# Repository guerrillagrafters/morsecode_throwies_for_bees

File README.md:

# morsecode_throwies_for_bees
This project builds off of the original throwie by Graffiti Research Labs (www.graffitiresearchlab.com), and the subsequent development of the morse code throwie using the ATTINY (http://www.instructables.com/id/Throwduino-Basic-Light-Sensing-Flashing-Throwie-/). Our morse code blinks out the names of fruits in Morse code. Use Ultraviolet LEDs to attract bees.

A lot more work could be done to make this code lighter. We welcome development!

What's needed:
 - Arduino or ATTiny programmer (Sparkfun sells one)
 - ATTiny85 (45 okay with some adjustments)
 - LEDs - we use Ultraviolet LEDs
 - Lithium coin cell battery
 - perf board for circuit, or custom designed circuit
 - electrical wire
 
 optional:
  - toggle switch
  - 270 or 330 resistor

To begin:
1) Make sure the Arduino programming environment is version 1.6.0 or above
2) In Arduino> Preferences, add the David Mellis attiny to boards manager URLs
     - Note: you might need to update boards.txt, manually writing in attiny45usbtinyisp.buildboard = COTE_ATTINY45USBTINYISP,        etc. 
3) Hook up your Arduino microcontroller, and run Arduino ISP from File> Examples
   - In the Tools menu, the board is set to "Arduino/ Genuino Uno", port is set to Arduino/ Uno, and the Programmer is AVR ISP
   - This is establishing the Arduino as a programmer for our ATTIny
4) Next, set up your ATTiny 85 on a breadboard. Schematic and image:
From High Low Tech's <a href="http://highlowtech.org/?p=1706">Arduino board as ATtiny programmer</a> article

From High Low Tech's <a href="http://highlowtech.org/?p=1695">Programming an ATtiny w/ Arduino 1.6 (or 1.0)</a> article

    - pins:
        - ATtiny Pin 2 to Arduino Pin 13 
        - ATtiny Pin 1 to Arduino Pin 12 
        - ATtiny Pin 0 to Arduino Pin 11
        - ATtiny Reset Pin to Arduino Pin 10 
   
5) Restart the Arduino code environment
6) In Tools> set the Board to ATTiny 25/45/85; Processor: ATTiny 85; Clock: Internal 1Mhz; Programmer: Arduino as ISP

6) Run "Blink" from File>Examples>Basics -- Change pin 13 to pin 0.
7) If blink is working, then we can now upload our morse code arduino code (above)
8) The basic schematic for the morse code throwie is here. I've also shared the eagle schematic and pcb design as a demonstration of how a creative design could be implemented using othermill. 

testing....

testing....

(Othermill can't handle these sharp lines, but hopefully will someday... this could be painted using conductive paint, or...)

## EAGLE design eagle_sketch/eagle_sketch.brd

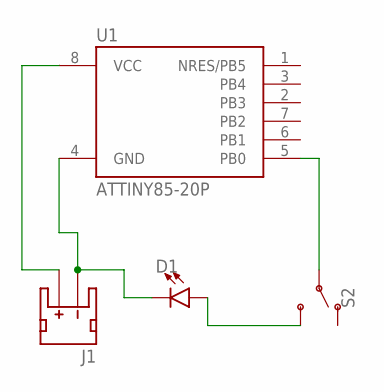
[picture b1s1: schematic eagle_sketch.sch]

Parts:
D1: LED3MM; LED_3MM
J1: JST_2MM_MALE; JST-2-SMD
S2: SWITCH-SPDT-PTH-11.6X4.0MM; SWITCH_SPDT_PTH_11.6X4.0MM
U1: ATTINY85-20P; PDIP08_300MIL

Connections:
unnamed: S2.2, U1.5 (PB0)
unnamed: D1.A, S2.3 (S)
unnamed: J1.2 (+), U1.8 (VCC)
unnamed: D1.K (C), J1.1 (-), U1.4 (GND)

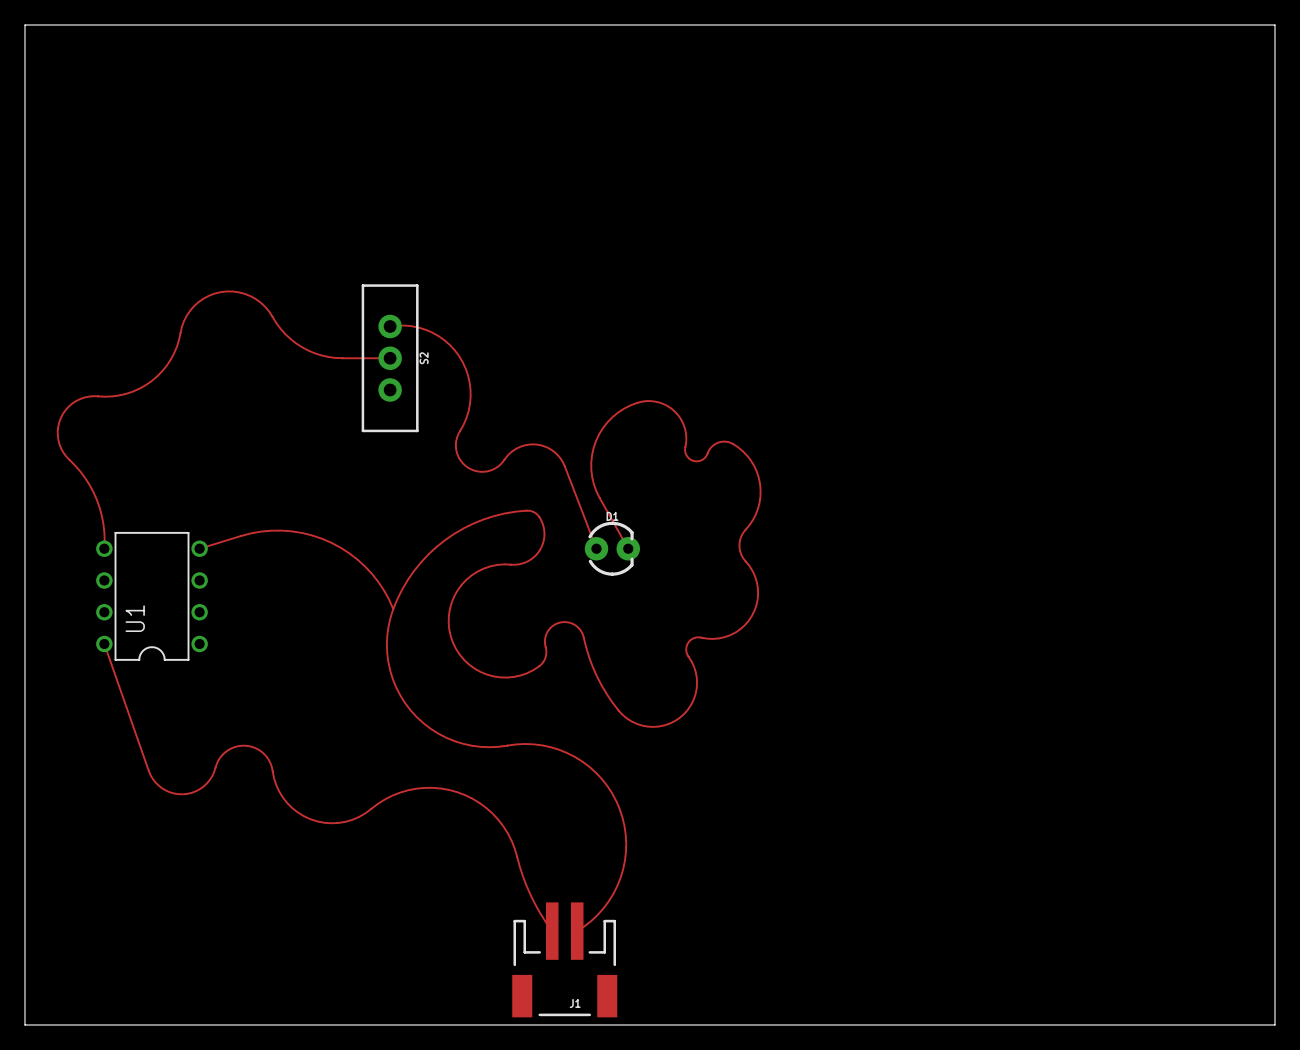
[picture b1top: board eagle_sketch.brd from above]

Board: 2 copper layers, 100.0 x 80.0 mm, 4 parts (0 on the bottom side), 4 nets.

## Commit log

2017-06-10 add arduino code
2017-06-10 add eagles sketches
2017-06-10 add list of ingredients

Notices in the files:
parts and their libraries:
SparkFun-LED: Licensing: Creative Commons ShareAlike 4.0 International - https://creativecommons.org/licenses/by-sa/4.0
